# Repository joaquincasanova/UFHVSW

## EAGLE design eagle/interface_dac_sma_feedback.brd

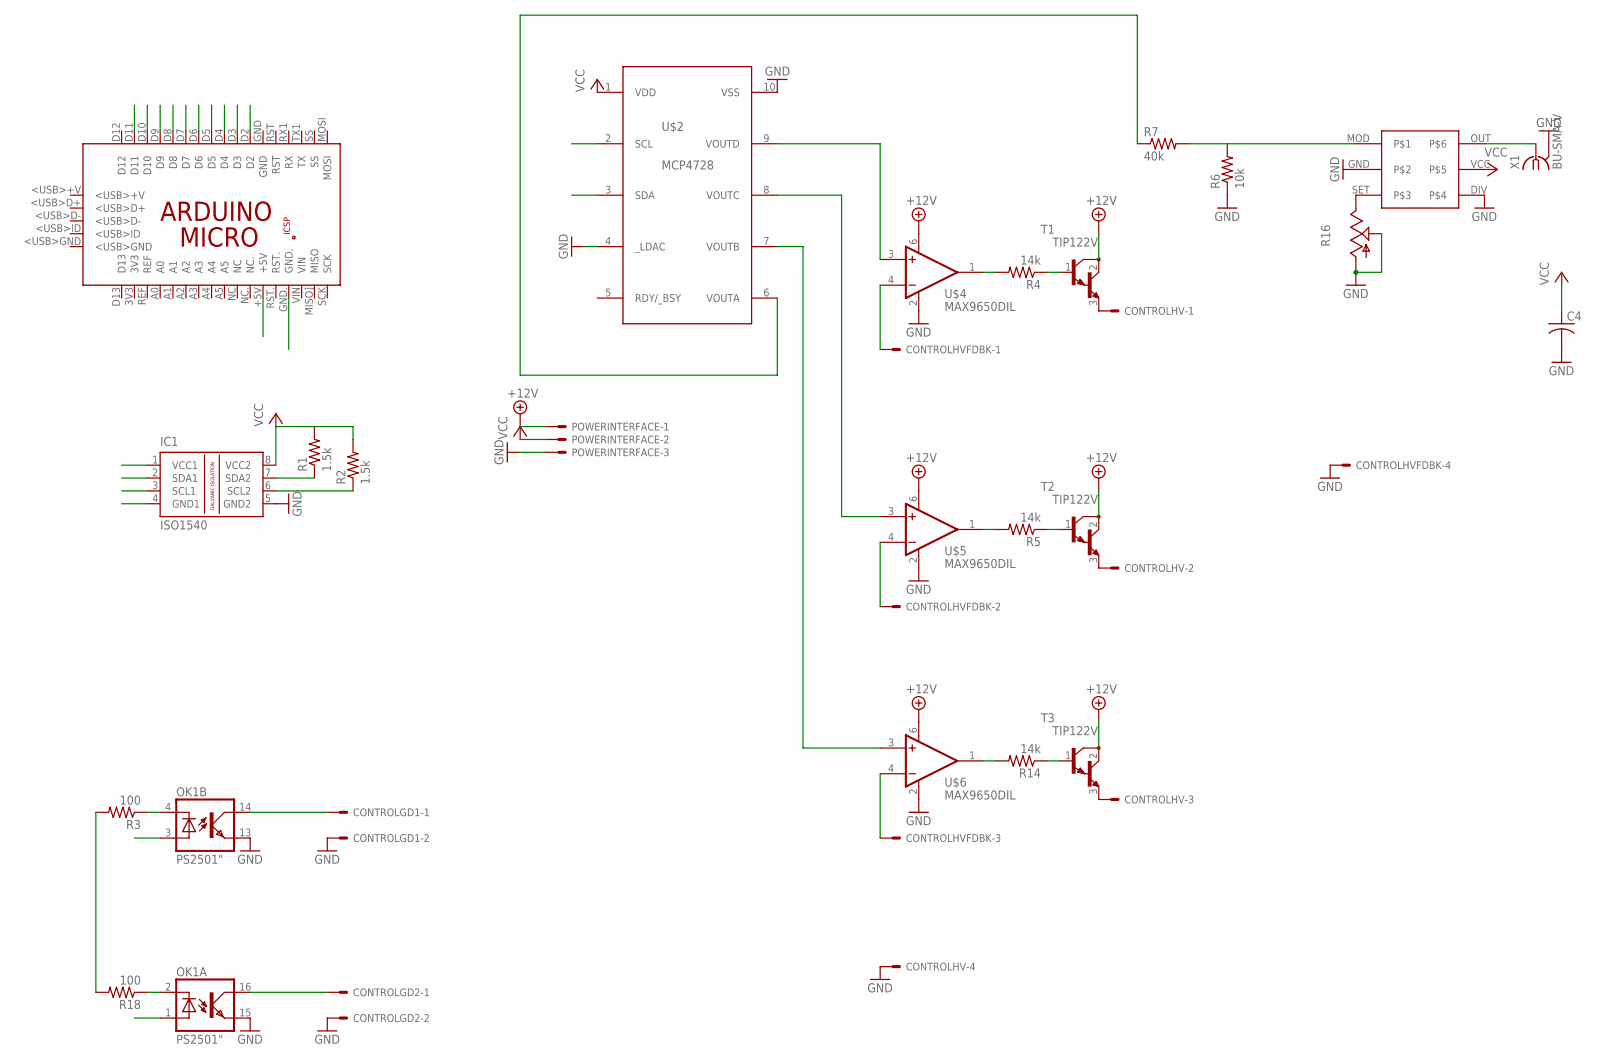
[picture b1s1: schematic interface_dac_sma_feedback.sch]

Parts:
C4: C-US075-063X106; C075-063X106
CONTROLGD1, CONTROLGD2: KK-156-2
CONTROLHV: KK-156-4
CONTROLHVFDBK: KK-156-4
IC1: ISO1540; DIL08
OK1: PS2501"; DIL16
PCB1: ARDUINO_MICRO
POWERINTERFACE: KK-156-3
R1, R2: 1.5k; 0207/12
R3, R18: 100; 0207/12
R4, R5, R14: 14k; 0207/12
R6: 10k; 0207/12
R7: 40k; 0207/12
R16: TRIM_US-B90P; SP19L
T1, T2, T3: TIP122V; TO220V
U$1: LTC6992; DIL06
U$2: MCP4728DIL; DIL10
U$4, U$5, U$6: MAX9650DIL; DIL06-4
X1: BU-SMA-V

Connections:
+12V: POWERINTERFACE.1, T1.2 (C), T2.2 (C), T3.2 (C), U$4.6 (V+), U$5.6 (V+), U$6.6 (V+)
A+5: IC1.1 (VCC1), PCB1.+5V
AGND: IC1.4 (GND1), PCB1.GND., R3.2, R18.2
D4: PCB1.D4
D7: PCB1.D7
D8: PCB1.D8
D10: PCB1.D10
D11: PCB1.D11
ENSW1: CONTROLGD1.1, OK1.14 (COL)
ENSW2: CONTROLGD2.1, OK1.16 (COL)
GND: C4.2, CONTROLGD1.2, CONTROLGD2.2, CONTROLHV.4, CONTROLHVFDBK.4, IC1.5 (GND2), OK1.13 (EMI), OK1.15 (EMI), POWERINTERFACE.3, R6.1, R16.A, R16.S, U$1.DIV, U$1.GND, U$2.4 (_LDAC), U$2.10 (VSS), U$4.2 (V-), U$5.2 (V-), U$6.2 (V-), X1.2, X1.3 (2), X1.4 (2), X1.5 (2)
unnamed: R7.1, U$2.6 (VOUTA)
unnamed: R6.2, R7.2, U$1.MOD
unnamed: R4.1, T1.1 (B)
unnamed: CONTROLHV.1, T1.3 (E)
unnamed: R5.1, T2.1 (B)
unnamed: CONTROLHV.2, T2.3 (E)
unnamed: OK1.2 (C), R18.1
unnamed: CONTROLHVFDBK.1, U$4.4 (-IN)
unnamed: CONTROLHVFDBK.2, U$5.4 (-IN)
unnamed: OK1.4 (C), R3.1
unnamed: CONTROLHV.3, T3.3 (E)
unnamed: R16.E, U$1.SET
unnamed: U$1.OUT, X1.1
unnamed: CONTROLHVFDBK.3, U$6.4 (-IN)
unnamed: R14.1, T3.1 (B)
unnamed: U$2.9 (VOUTD), U$4.3 (+IN)
unnamed: U$2.8 (VOUTC), U$5.3 (+IN)
unnamed: U$2.7 (VOUTB), U$6.3 (+IN)
unnamed: R4.2, U$4.1 (OUT)
unnamed: R5.2, U$5.1 (OUT)
unnamed: R14.2, U$6.1 (OUT)
PWM5: PCB1.D5
PWM6: OK1.3 (A), PCB1.D6
PWM9: OK1.1 (A), PCB1.D9
SCL: IC1.3 (SCL1), PCB1.D3
SCL_OUT: IC1.6 (SCL2), R2.1, U$2.2 (SCL)
SDA: IC1.2 (SDA1), PCB1.D2
SDA_OUT: IC1.7 (SDA2), R1.1, U$2.3 (SDA)
VCC: C4.1, IC1.8 (VCC2), POWERINTERFACE.2, R1.2, R2.2, U$1.VCC, U$2.1 (VDD)

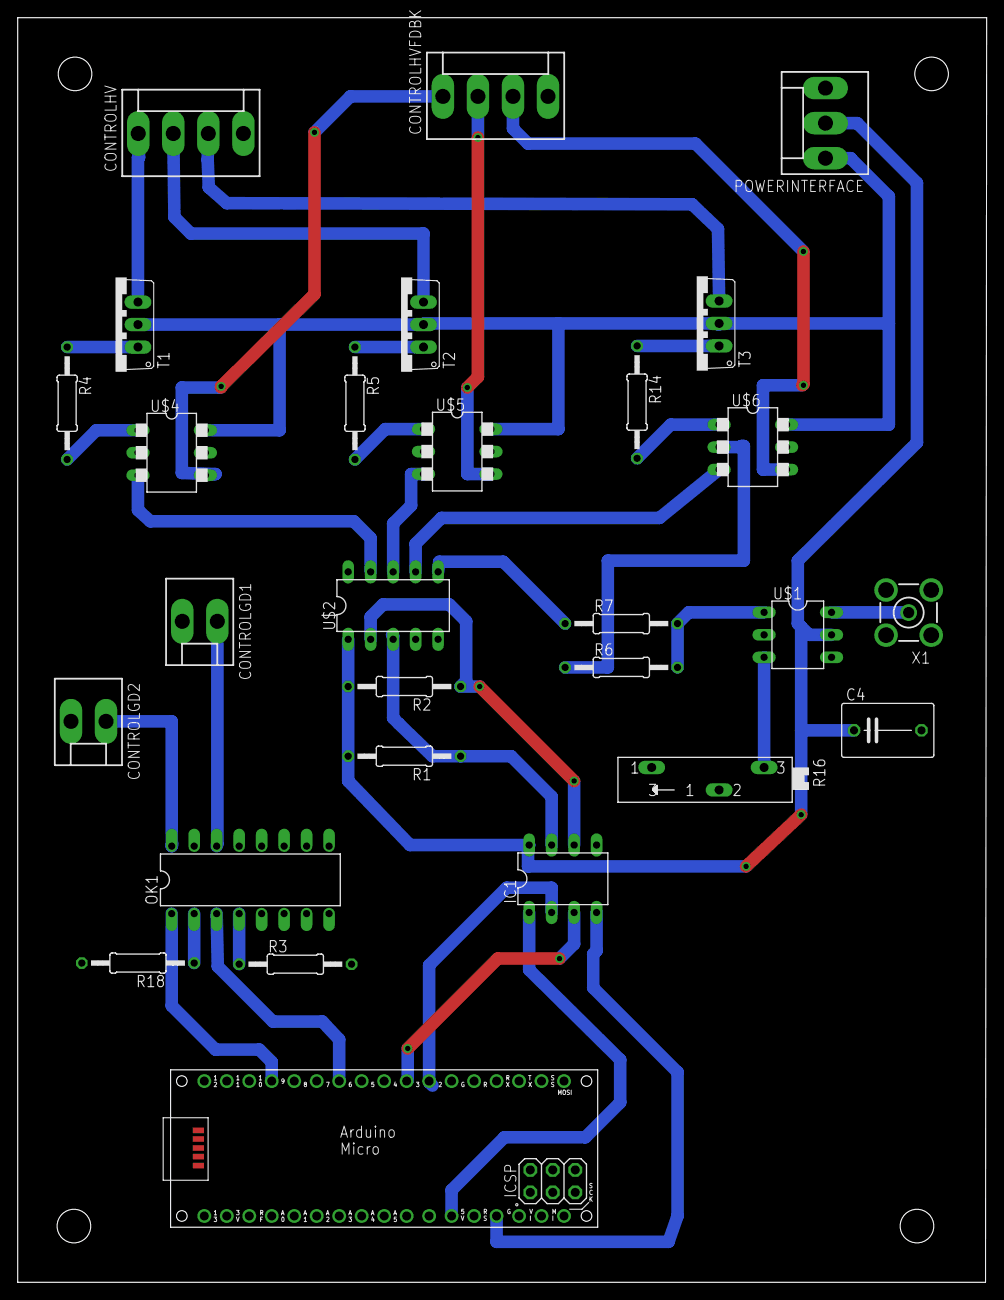
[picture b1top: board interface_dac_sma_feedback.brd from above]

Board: 2 copper layers, 109.5 x 142.9 mm, 28 parts (0 on the bottom side), 34 nets.

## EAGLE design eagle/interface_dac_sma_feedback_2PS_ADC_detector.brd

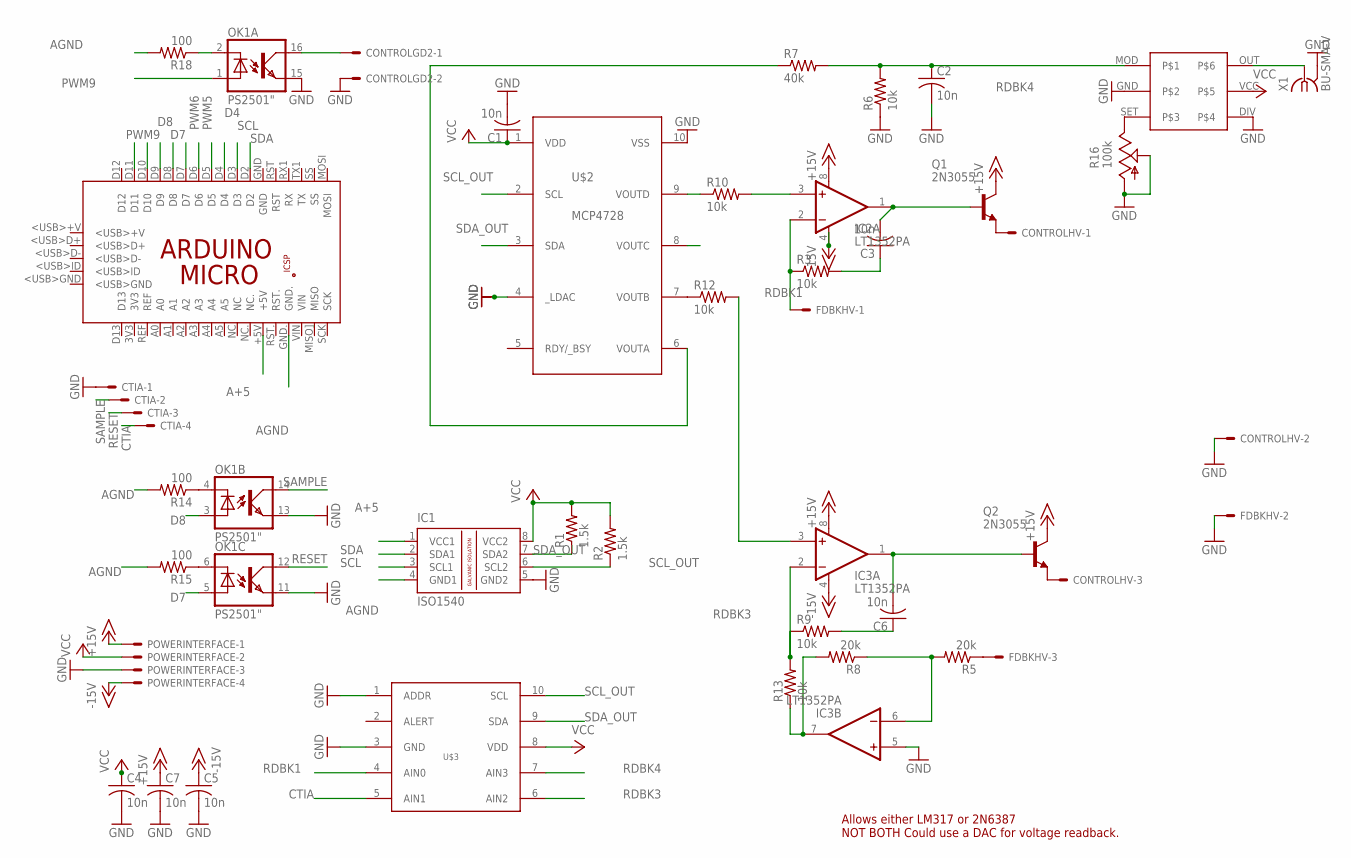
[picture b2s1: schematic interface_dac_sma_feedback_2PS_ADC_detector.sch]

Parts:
C1, C2, C3, C4, C5, C6, C7: 10n; C050-024X044
CONTROLGD2: KK-156-2
CONTROLHV: KK-156-3
CTIA: KK-156-4
FDBKHV: KK-156-3
IC1: ISO1540; DIL08
IC2, IC3: LT1352PA; DIL08
OK1: PS2501"; DIL16
PCB1: ARDUINO_MICRO
POWERINTERFACE: KK-156-4
Q1, Q2: 2N3055; TO3
R1, R2: 1.5k; 0207/12
R3, R6, R9, R10, R12, R13: 10k; 0207/12
R5, R8: 20k; 0207/12
R7: 40k; 0207/12
R14, R15, R18: 100; 0207/12
R16: 100k; SP19L
U$1: LTC6992; DIL06
U$2: MCP4728DIL; DIL10
U$3: ADS1015DIL; DIL10
X1: BU-SMA-V

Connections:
+15V: C7.1, IC2.8 (V+), IC3.8 (V+), POWERINTERFACE.1, Q1.C, Q1.C/ (C), Q2.C, Q2.C/ (C)
-15V: C5.1, IC2.4 (V-), IC3.4 (V-), POWERINTERFACE.4
A+5: IC1.1 (VCC1), PCB1.+5V
AGND: IC1.4 (GND1), PCB1.GND., R14.2, R15.2, R18.2
CTIA: CTIA.4, U$3.5 (AIN1)
D4: PCB1.D4
D7: OK1.5 (A), PCB1.D7
D8: OK1.3 (A), PCB1.D8
D10: PCB1.D10
D11: PCB1.D11
ENSW2: CONTROLGD2.1, OK1.16 (COL)
GND: C1.2, C2.2, C4.2, C5.2, C7.2, CONTROLGD2.2, CONTROLHV.2, CTIA.1, FDBKHV.2, IC1.5 (GND2), IC3.5 (+IN), OK1.11 (EMI), OK1.13 (EMI), OK1.15 (EMI), POWERINTERFACE.3, R6.1, R16.A, R16.S, U$1.DIV, U$1.GND, U$2.4 (_LDAC), U$2.10 (VSS), U$3.1 (ADDR), U$3.3 (GND), X1.2, X1.3 (2), X1.4 (2), X1.5 (2)
unnamed: R7.1, U$2.6 (VOUTA)
unnamed: OK1.4 (C), R14.1
unnamed: C3.1, R3.2
unnamed: CONTROLHV.1, Q1.E
unnamed: CONTROLHV.3, Q2.E
unnamed: OK1.6 (C), R15.1
unnamed: OK1.2 (C), R18.1
unnamed: FDBKHV.3, R5.1
unnamed: R16.E, U$1.SET
unnamed: U$1.OUT, X1.1
unnamed: IC3.7 (OUT), R8.2, R13.1
unnamed: IC2.3 (+IN), R10.2
unnamed: IC3.3 (+IN), R12.2
unnamed: C3.2, IC2.1 (OUT), Q1.B
unnamed: C6.1, R9.2
unnamed: C6.2, IC3.1 (OUT), Q2.B
unnamed: IC3.6 (-IN), R5.2, R8.1
unnamed: R10.1, U$2.9 (VOUTD)
unnamed: R12.1, U$2.7 (VOUTB)
PWM5: PCB1.D5
PWM6: PCB1.D6
PWM9: OK1.1 (A), PCB1.D9
RDBK1: FDBKHV.1, IC2.2 (-IN), R3.1, U$3.4 (AIN0)
RDBK3: IC3.2 (-IN), R9.1, R13.2, U$3.6 (AIN2)
RDBK4: C2.1, R6.2, R7.2, U$1.MOD, U$3.7 (AIN3)
RESET: CTIA.3, OK1.12 (COL)
SAMPLE: CTIA.2, OK1.14 (COL)
SCL: IC1.3 (SCL1), PCB1.D3
SCL_OUT: IC1.6 (SCL2), R2.1, U$2.2 (SCL), U$3.10 (SCL)
SDA: IC1.2 (SDA1), PCB1.D2
SDA_OUT: IC1.7 (SDA2), R1.1, U$2.3 (SDA), U$3.9 (SDA)
VCC: C1.1, C4.1, IC1.8 (VCC2), POWERINTERFACE.2, R1.2, R2.2, U$1.VCC, U$2.1 (VDD), U$3.8 (VDD)

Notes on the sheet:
Allows either LM317 or 2N6387 NOT BOTH Could use a DAC for voltage readback.

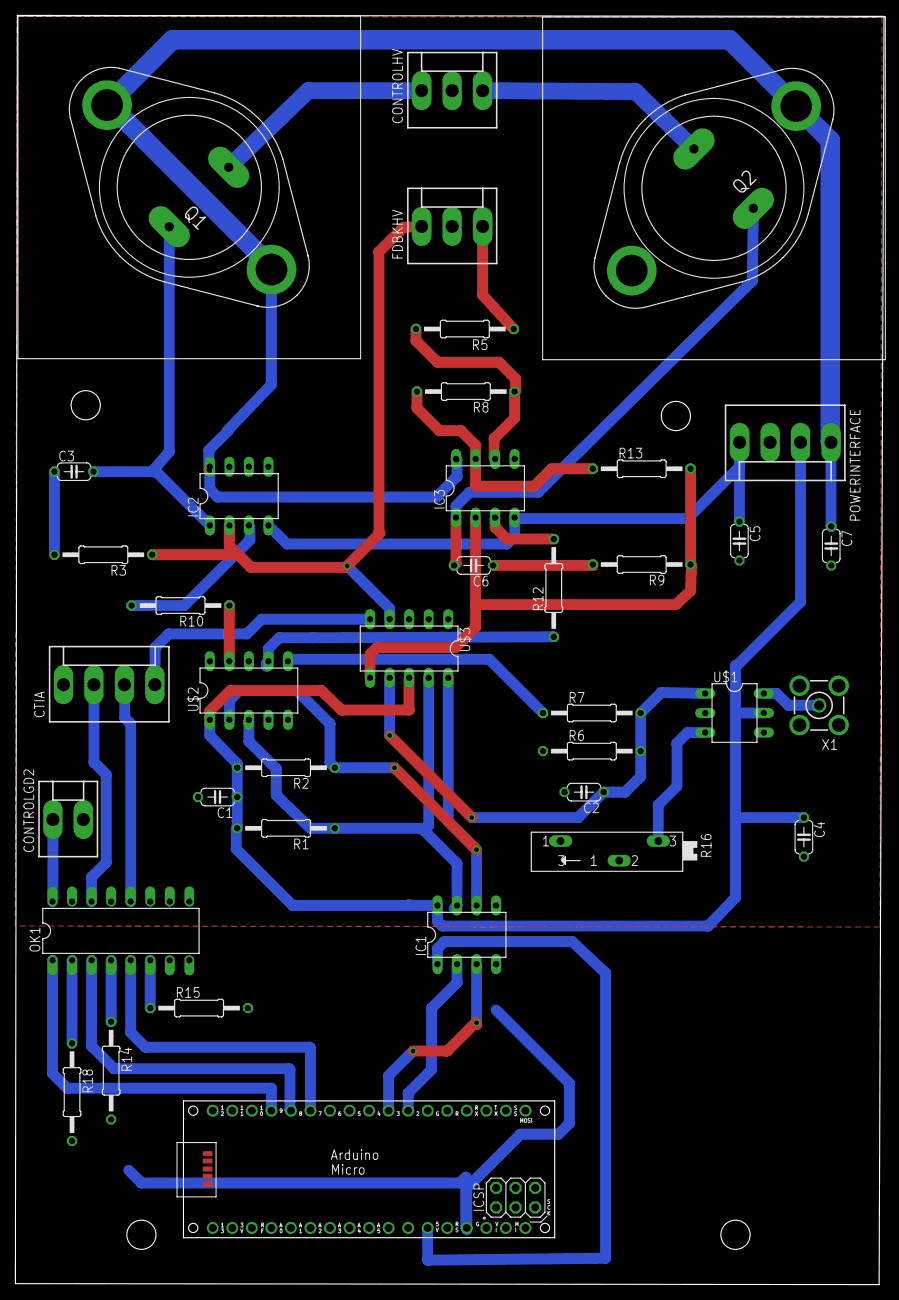
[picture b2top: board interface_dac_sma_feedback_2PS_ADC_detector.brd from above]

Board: 2 copper layers, 112.9 x 165.0 mm, 38 parts (0 on the bottom side), 39 nets.

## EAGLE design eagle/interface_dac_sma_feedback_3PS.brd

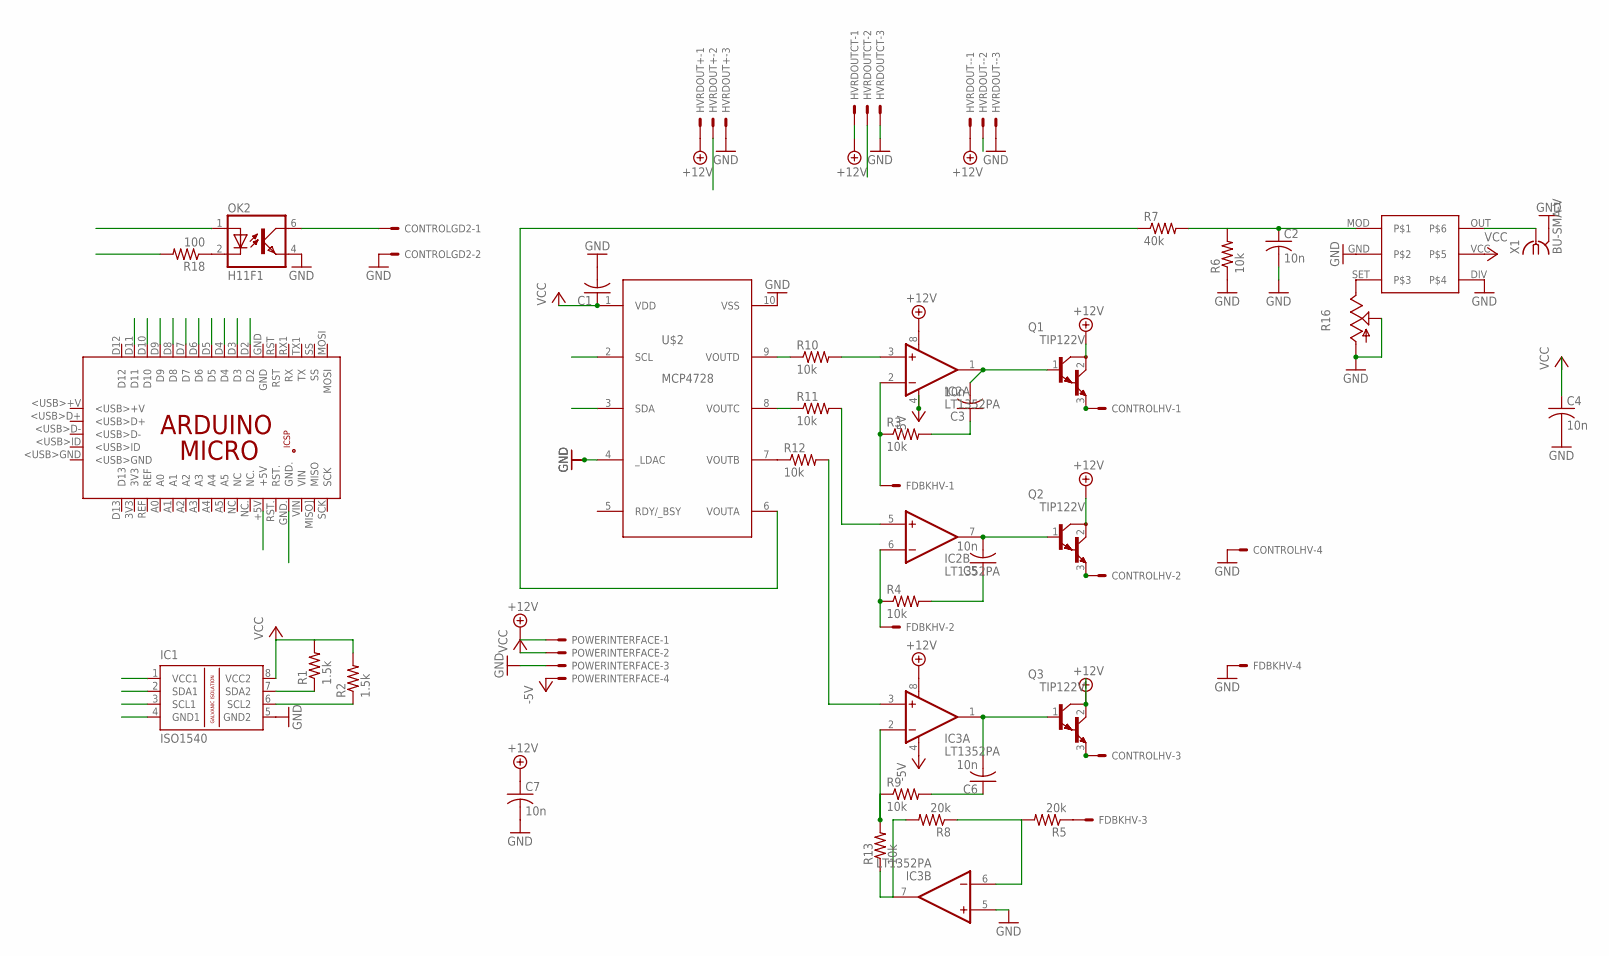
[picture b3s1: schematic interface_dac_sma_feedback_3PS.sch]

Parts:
C1: C-US050-050X075; C050-050X075
C2, C3, C5, C6: 10n; C050-024X044
C4: 10n; C075-063X106
C7: 10n; C050-050X075
CONTROLGD2: KK-156-2
CONTROLHV: KK-156-4
FDBKHV: KK-156-4
HVRDOUT+: KK-156-3
HVRDOUT-: KK-156-3
HVRDOUTCT: KK-156-3
IC1: ISO1540; DIL08
IC2, IC3: LT1352PA; DIL08
OK2: H11F1; DIL05
PCB1: ARDUINO_MICRO
POWERINTERFACE: KK-156-4
Q1, Q2, Q3: TIP122V; TO220V
R1, R2: 1.5k; 0207/12
R3, R4, R6, R9, R10, R11, R12, R13: 10k; 0207/12
R5, R8: 20k; 0207/12
R7: 40k; 0207/12
R16: TRIM_US-B90P; SP19L
R18: 100; 0207/12
U$1: LTC6992; DIL06
U$2: MCP4728DIL; DIL10
X1: BU-SMA-V

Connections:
+12V: C7.1, HVRDOUT+.1, HVRDOUT-.1, HVRDOUTCT.1, IC2.8 (V+), IC3.8 (V+), POWERINTERFACE.1, Q1.2 (C), Q2.2 (C), Q3.2 (C)
-5V: IC2.4 (V-), IC3.4 (V-), POWERINTERFACE.4
A+5: IC1.1 (VCC1), PCB1.+5V
AGND: IC1.4 (GND1), PCB1.GND., R18.2
D4: PCB1.D4
D7: PCB1.D7
D8: PCB1.D8
D10: PCB1.D10
D11: PCB1.D11
ENSW2: CONTROLGD2.1, OK2.6 (COL)
GND: C1.2, C2.2, C4.2, C7.2, CONTROLGD2.2, CONTROLHV.4, FDBKHV.4, HVRDOUT+.3, HVRDOUT-.3, HVRDOUTCT.3, IC1.5 (GND2), IC3.5 (+IN), OK2.4 (EMIT), POWERINTERFACE.3, R6.1, R16.A, R16.S, U$1.DIV, U$1.GND, U$2.4 (_LDAC), U$2.10 (VSS), X1.2, X1.3 (2), X1.4 (2), X1.5 (2)
unnamed: R7.1, U$2.6 (VOUTA)
unnamed: C2.1, R6.2, R7.2, U$1.MOD
unnamed: C3.1, R3.2
unnamed: CONTROLHV.1, Q1.3 (E)
unnamed: CONTROLHV.3, Q3.3 (E)
unnamed: FDBKHV.2, HVRDOUTCT.2, IC2.6 (-IN), R4.1
unnamed: OK2.2 (C), R18.1
unnamed: FDBKHV.1, HVRDOUT+.2, IC2.2 (-IN), R3.1
unnamed: FDBKHV.3, R5.1
unnamed: C5.2, IC2.7 (OUT), Q2.1 (B)
unnamed: CONTROLHV.2, Q2.3 (E)
unnamed: R16.E, U$1.SET
unnamed: U$1.OUT, X1.1
unnamed: HVRDOUT-.2, IC3.7 (OUT), R8.2, R13.1
unnamed: C5.1, R4.2
unnamed: IC2.3 (+IN), R10.2
unnamed: IC2.5 (+IN), R11.2
unnamed: IC3.3 (+IN), R12.2
unnamed: C3.2, IC2.1 (OUT), Q1.1 (B)
unnamed: C6.1, R9.2
unnamed: C6.2, IC3.1 (OUT), Q3.1 (B)
unnamed: IC3.6 (-IN), R5.2, R8.1
unnamed: R10.1, U$2.9 (VOUTD)
unnamed: R12.1, U$2.7 (VOUTB)
unnamed: R11.1, U$2.8 (VOUTC)
unnamed: IC3.2 (-IN), R9.1, R13.2
PWM5: PCB1.D5
PWM6: PCB1.D6
PWM9: OK2.1 (A), PCB1.D9
SCL: IC1.3 (SCL1), PCB1.D3
SCL_OUT: IC1.6 (SCL2), R2.1, U$2.2 (SCL)
SDA: IC1.2 (SDA1), PCB1.D2
SDA_OUT: IC1.7 (SDA2), R1.1, U$2.3 (SDA)
VCC: C1.1, C4.1, IC1.8 (VCC2), POWERINTERFACE.2, R1.2, R2.2, U$1.VCC, U$2.1 (VDD)

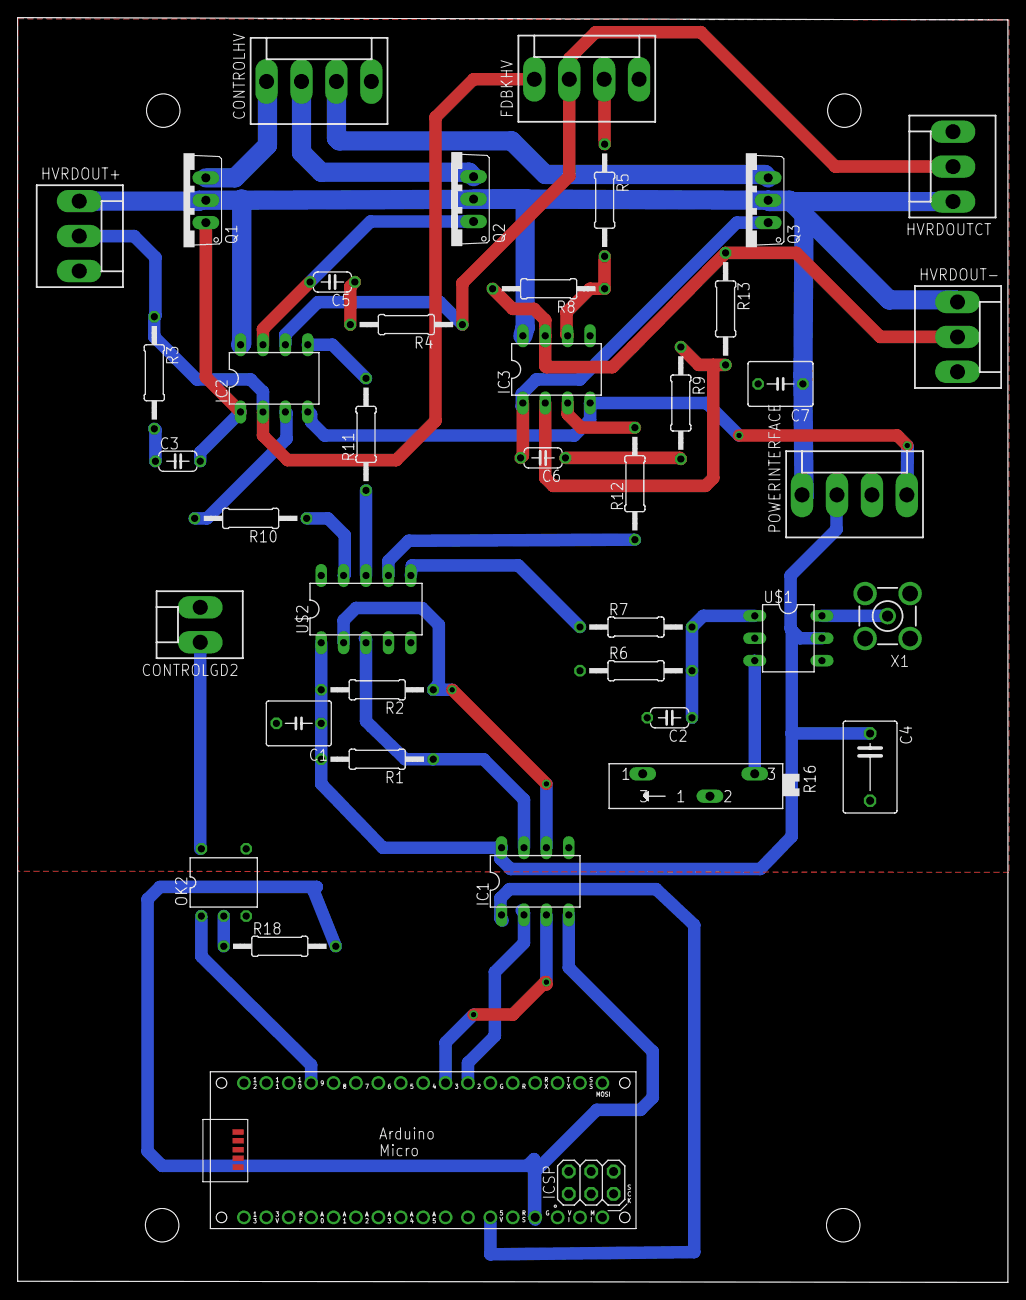
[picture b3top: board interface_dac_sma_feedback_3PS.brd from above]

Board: 2 copper layers, 112.3 x 143.4 mm, 40 parts (0 on the bottom side), 38 nets.
